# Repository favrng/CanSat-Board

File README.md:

### CanSat Payload Board

Made for Narantaka of Gadjah Mada Aerospace Team in 2022 Annual CanSat Competition held by American Astronautical Society (AAS).

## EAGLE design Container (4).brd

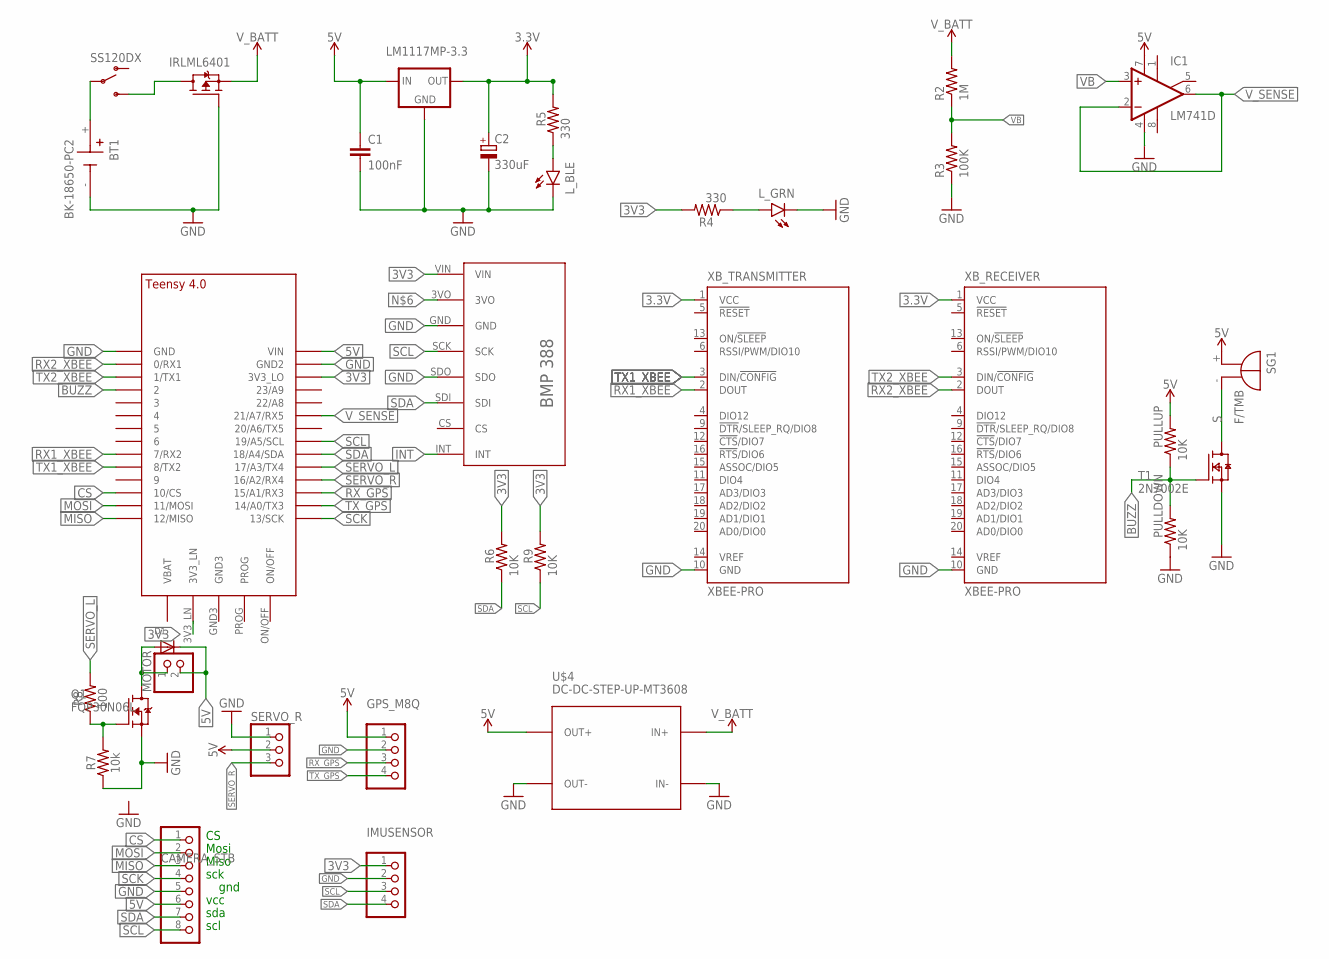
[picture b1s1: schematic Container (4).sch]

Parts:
BT1: BK-18650-PC2; BAT_BK-18650-PC2
C1: 100nF; C0805
C2: 330uF; D/7343-31W
CAMERA_STB: PINHD-1X8; 1X08
D1: DIODEDO-1N4148; DO-1N4148
GPS_M8Q: PINHD-1X4; 1X04
IC1: LM741D; SO08
IC2: LM1117MP-3.3; SOT223
IMUSENSOR: PINHD-1X4; 1X04
IRLML6401: MOSFET-PWIDE; SOT23-WIDE
L_BLE: LED1206; LED-1206
L_GRN: LED1206; LED-1206
MOTOR: PINHD-1X2; 1X02
PULLDOWN: 10K; M0805
PULLUP: 10K; M0805
Q1: FQP30N06L; TO220V
R2: 1M; M1206
R3: 100K; M1206
R4, R5: 330; M0805
R6, R9: 10K; M0805
R7: 10k; 0805
R8: 100; 0805
SERVO_R: PINHD-1X3; 1X03
SG1: F/TMB
T1: 2N7002E; SOT23
U$1: TEENSY_4.0-BASIC
U$2: BMP388
U$3: SS120DX; SS12D0X
U$4: DC-DC-STEP-UP-MT3608
XB_RECEIVER: XBEE-PRO
XB_TRANSMITTER: XBEE-PRO

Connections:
3.3V: C2.+, IC2.2 (OUT), IC2.4 (OUT), R5.2, XB_RECEIVER.1 (VCC), XB_TRANSMITTER.1 (VCC)
3V3: IMUSENSOR.1, R4.2, R6.2, R9.2, U$1.3V3_LN, U$1.3V3_LO, U$2.VIN
5V: C1.1, CAMERA_STB.6, D1.C, GPS_M8Q.1, IC1.7 (V+), IC2.3 (IN), MOTOR.2, PULLUP.2, SERVO_R.2, SG1.+, U$1.VIN, U$4.OUT+
BUZZ: PULLDOWN.2, PULLUP.1, T1.1 (G), U$1.2
CS: CAMERA_STB.1, U$1.10/CS
GND: BT1.-, C1.2, C2.-, CAMERA_STB.5, GPS_M8Q.2, IC1.4 (V-), IC2.1 (GND), IMUSENSOR.2, IRLML6401.1 (G), L_BLE.C, L_GRN.C, PULLDOWN.1, Q1.3 (S), R3.1, R7.1, SERVO_R.1, T1.2 (S), U$1.GND, U$1.GND2, U$2.GND, U$2.SDO, U$4.IN-, U$4.OUT-, XB_RECEIVER.10 (GND), XB_TRANSMITTER.10 (GND)
INT: U$2.INT
MISO: CAMERA_STB.3, U$1.12/MISO
MOSI: CAMERA_STB.2, U$1.11/MOSI
unnamed: IRLML6401.3 (D), U$3.3
unnamed: Q1.1 (G), R7.2, R8.1
unnamed: L_GRN.A, R4.1
unnamed: D1.A, MOTOR.1, Q1.2 (D)
unnamed: L_BLE.A, R5.1
NSSS: BT1.+, U$3.2
RX1_XBEE: U$1.7 (7/RX2), XB_TRANSMITTER.2 (DOUT)
RX2_XBEE: U$1.0/RX (0/RX1), XB_RECEIVER.2 (DOUT)
RX_GPS: GPS_M8Q.3, U$1.15/A1 (15/A1/RX3)
S: SG1.-, T1.3 (D)
SCK: CAMERA_STB.4, U$1.13/SCK
SCL: CAMERA_STB.8, IMUSENSOR.3, R9.1, U$1.19/A5/SCL, U$2.SCK
SDA: CAMERA_STB.7, IMUSENSOR.4, R6.1, U$1.18/A4/SDA, U$2.SDI
SERVO_L: R8.2, U$1.17/A3 (17/A3/TX4)
SERVO_R: SERVO_R.3, U$1.16/A2 (16/A2/RX4)
TX1_XBEE: U$1.8 (8/TX2), XB_TRANSMITTER.3 (DIN/!CONFIG)
TX2_XBEE: U$1.1/TX (1/TX1), XB_RECEIVER.3 (DIN/!CONFIG)
TX_GPS: GPS_M8Q.4, U$1.14/A0 (14/A0/TX3)
VB: IC1.3 (+IN), R2.1, R3.2
V_BATT: IRLML6401.2 (S), R2.2, U$4.IN+
V_SENSE: IC1.2 (-IN), IC1.6 (OUT), U$1.21/A7 (21/A7/RX5)

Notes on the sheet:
Mosi
Miso
sck
gnd
vcc
sda
scl

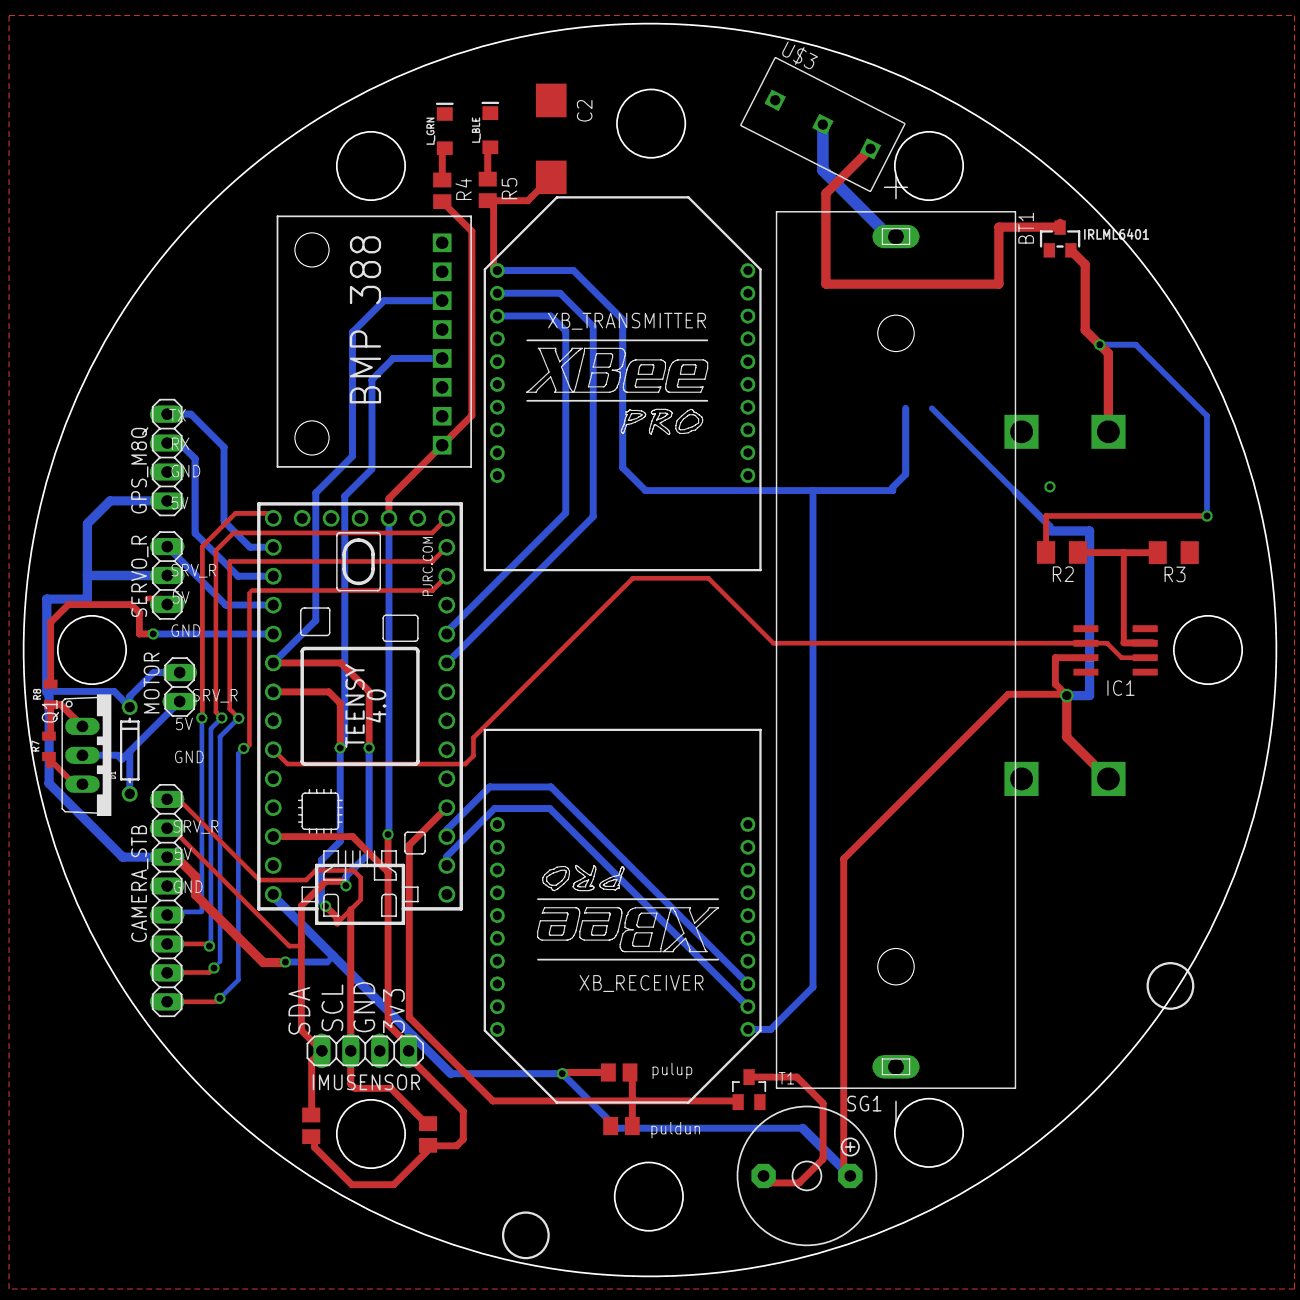
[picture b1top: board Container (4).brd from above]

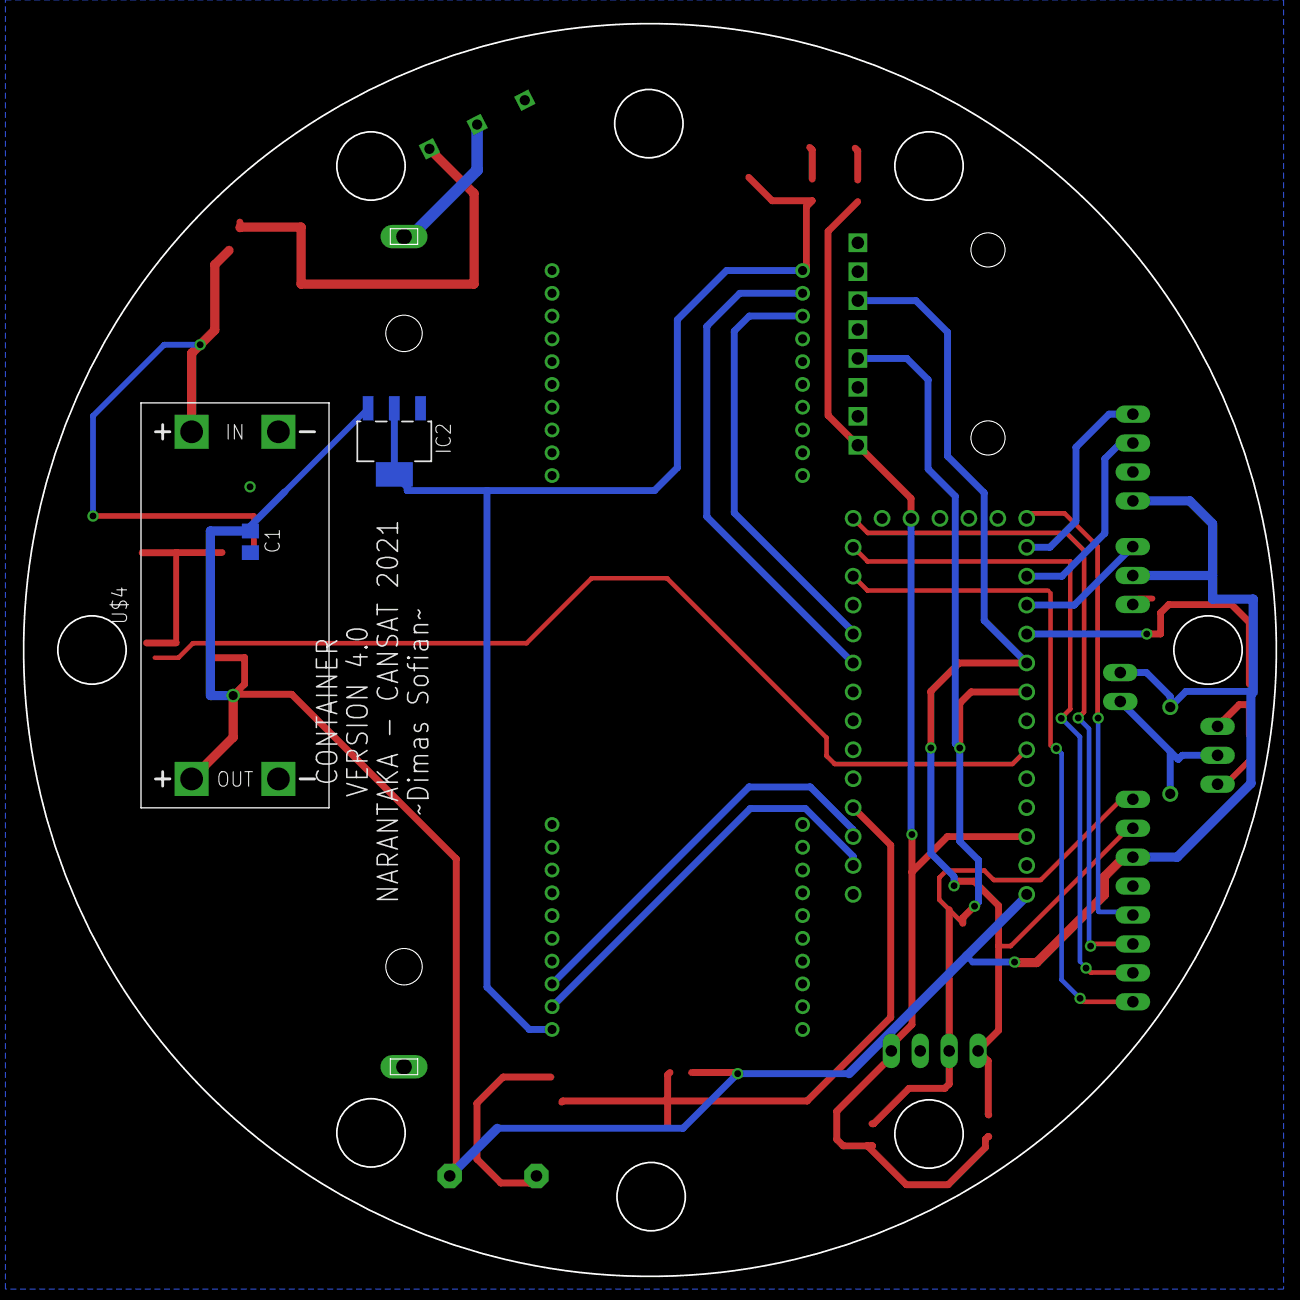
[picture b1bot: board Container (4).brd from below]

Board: 2 copper layers, 110.0 x 110.0 mm, 33 parts (3 on the bottom side), 29 nets.

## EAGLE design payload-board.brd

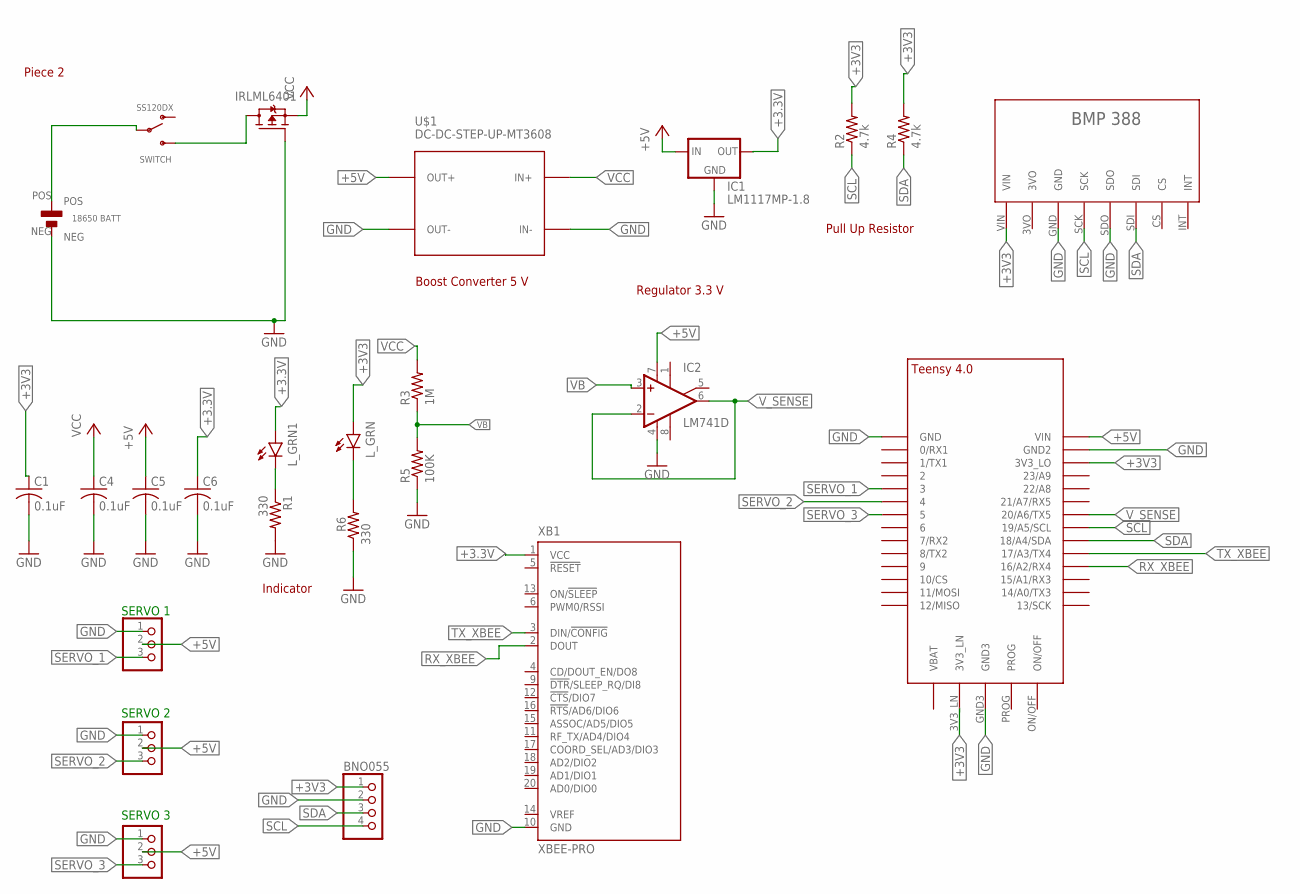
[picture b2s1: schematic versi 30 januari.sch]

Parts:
BNO055: PINHD-1X4; 1X04
C1, C4, C5, C6: 0.1uF; C0805
IC1: LM1117MP-1.8; SOT223
IC2: LM741D; SO08
IRLML6401: MOSFET-PWIDE; SOT23-WIDE
L_GRN, L_GRN1: LED1206; LED-1206
R1, R6: 330; M0805
R2, R4: 4.7k; M0805
R3: 1M; M1206
R5: 100K; M1206
SERVO1, SERVO2, SERVO3: PINHD-1X3; 1X03
SWITCH: SS120DX; SS12D0X
U$1: DC-DC-STEP-UP-MT3608
U$3: BMP388
U$4: 18650
U$6: TEENSY_4.0
XB1: XBEE-PRO

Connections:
+3.3V: C6.1, IC1.2 (OUT), IC1.4 (OUT), L_GRN1.A, XB1.1 (VCC)
+3V3: BNO055.1, C1.1, L_GRN.A, R2.2, R4.2, U$3.VIN, U$6.3V3_LN, U$6.3V3_LO
+5V: C5.1, IC1.3 (IN), IC2.7 (V+), SERVO1.2, SERVO2.2, SERVO3.2, U$1.OUT+, U$6.VIN
GND: BNO055.2, C1.2, C4.2, C5.2, C6.2, IC1.1 (GND), IC2.4 (V-), IRLML6401.1 (G), R1.2, R5.1, R6.1, SERVO1.1, SERVO2.1, SERVO3.1, U$1.IN-, U$1.OUT-, U$3.GND, U$3.SDO, U$4.NEG, U$6.GND, U$6.GND2, U$6.GND3, XB1.10 (GND)
unnamed: SWITCH.2, U$4.POS
unnamed: L_GRN.C, R6.2
unnamed: IRLML6401.3 (D), SWITCH.3
unnamed: L_GRN1.C, R1.1
RX_XBEE: U$6.16/A2 (16/A2/RX4), XB1.2 (DOUT)
SCL: BNO055.4, R2.1, U$3.SCK, U$6.19/A5/SCL
SDA: BNO055.3, R4.1, U$3.SDI, U$6.18/A4/SDA
SERVO_1: SERVO1.3, U$6.3/CANTX (3)
SERVO_2: SERVO2.3, U$6.4/CANRX (4)
SERVO_3: SERVO3.3, U$6.5
TX_XBEE: U$6.17/A3 (17/A3/TX4), XB1.3 (DIN/!CONFIG)
VB: IC2.3 (+IN), R3.1, R5.2
VCC: C4.1, IRLML6401.2 (S), R3.2, U$1.IN+
V_SENSE: IC2.2 (-IN), IC2.6 (OUT), U$6.20/A6 (20/A6/TX5)

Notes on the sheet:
Boost Converter 5 V
Regulator 3.3 V
Indicator
Pull Up Resistor
Piece 2
SERVO 2
SERVO 1
SERVO 3

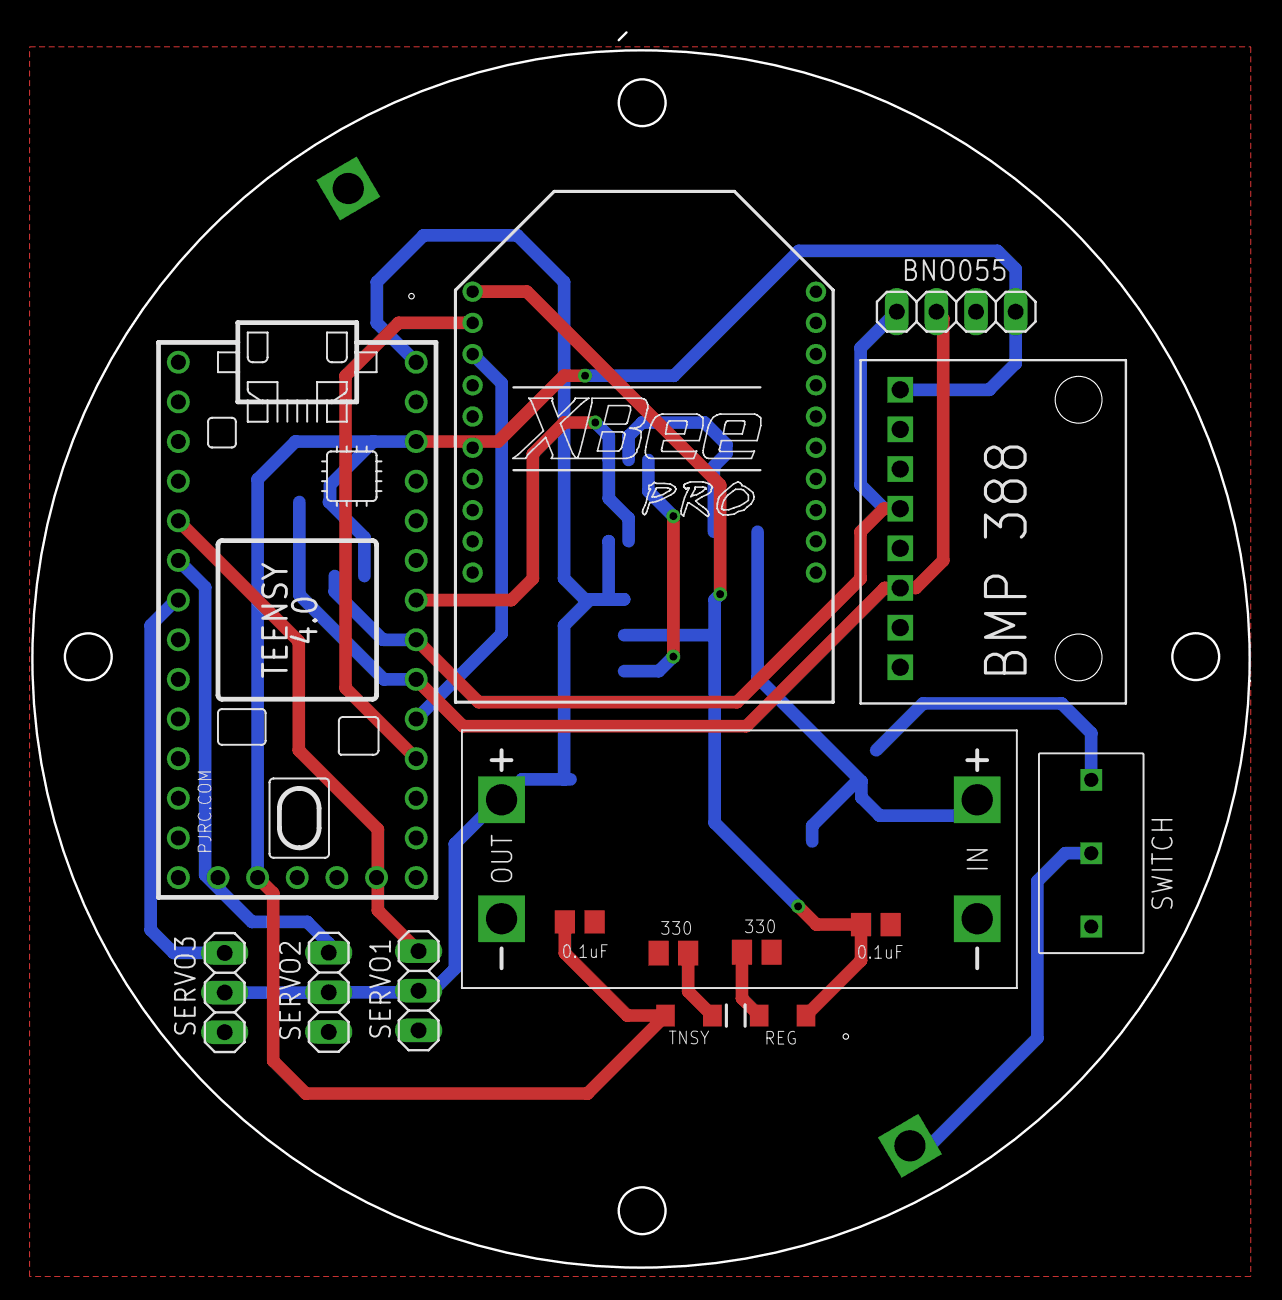
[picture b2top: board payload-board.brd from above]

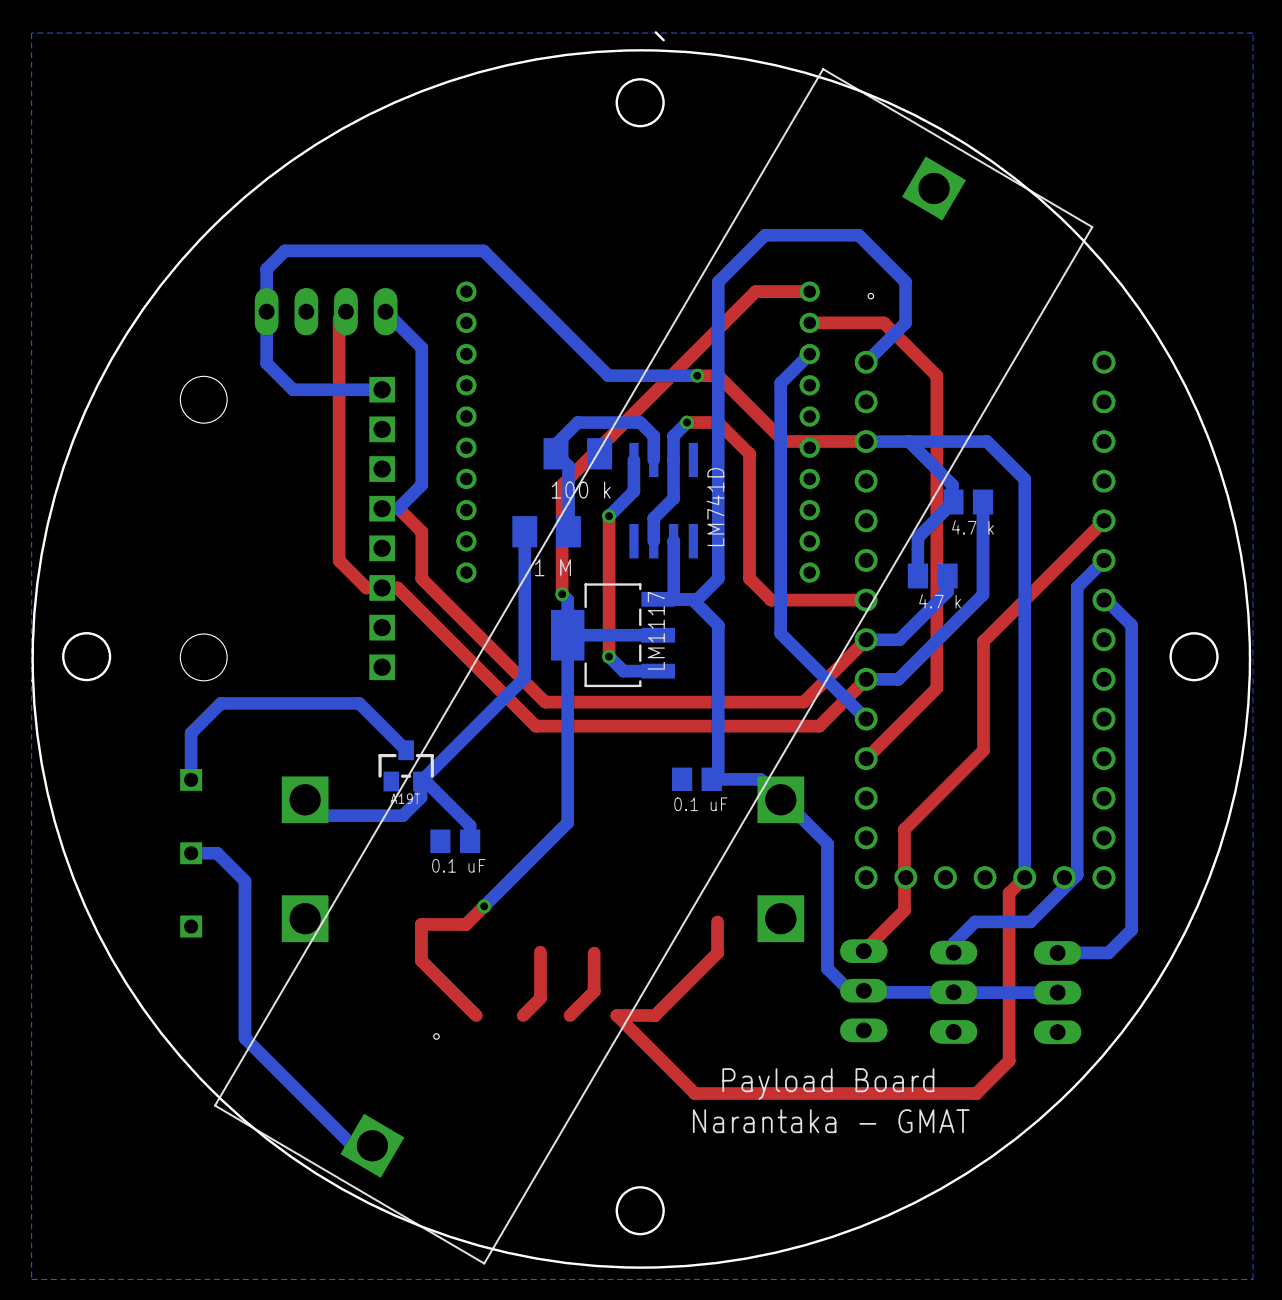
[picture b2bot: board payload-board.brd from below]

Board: 2 copper layers, 78.0 x 79.2 mm, 25 parts (10 on the bottom side), 18 nets.

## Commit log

2022-05-09 Uploading brd
2022-05-09 renamed
2023-11-01 Rename board.brd to payload-board.brd
2023-11-01 Rename schematic.sch to payload-schematic.sch
2023-11-01 Added container files
2023-11-01 Rename Container (4).sch to container-schematic.sch
2023-11-01 Rename Container (4).brd to container-boardbrd

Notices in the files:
parts and their libraries:
microbuilder: This work is placed in the public domain, and may be freely used for commercial and non-commercial work with the following conditions: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
SparkFun-LED: Licensing: Creative Commons ShareAlike 4.0 International - https://creativecommons.org/licenses/by-sa/4.0
